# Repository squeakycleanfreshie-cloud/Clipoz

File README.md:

# Clipoz
The keychain that tracks movement

**What are Clipoz?**
Clipoz are small 3D printable keychains, that track movement. When the movement is triggered between certain times, a notification is sent to select Mates, telling them that your on the move!

**How are clipoz useful?**
Clipoz are perfect for school freinds, who walk the same route to school, but pass eachothers houses at different times. They tell your freind when you leave, without telling them where you are - which removes lots of privacy concens.

**Why did I create Clipoz?**
I created clipoz because I wanted to meet up with my freind at the bus stop without missing him, because he is really forgetful and won't text me. 

**Why do they look like that?**
Clipoz are themed in different fruits, printing in packs of three. I want to make them into a blind box sort of system. maybe one day.

**Assembly Instructions**
1. 3D Print the fruits body, screws and back/lid
2. Solder the parts to the custom PCB, making sure everything is good.
3. Insert the PCB into the back of the Fruits
4. Add an optional keychain if you want to
5. Setup the bot, edit the code to your setting - more info found in guide in docs.
6. Have fun using them.

Onshape Link: https://cad.onshape.com/documents/c4d0343753f5ce60cb524a63/w/d55154f7bbc865e658fab8c6/e/a9e77f0447d58db2c40de487?renderMode=0&uiState=6a01ac4ed3c7c0f6100e28a5

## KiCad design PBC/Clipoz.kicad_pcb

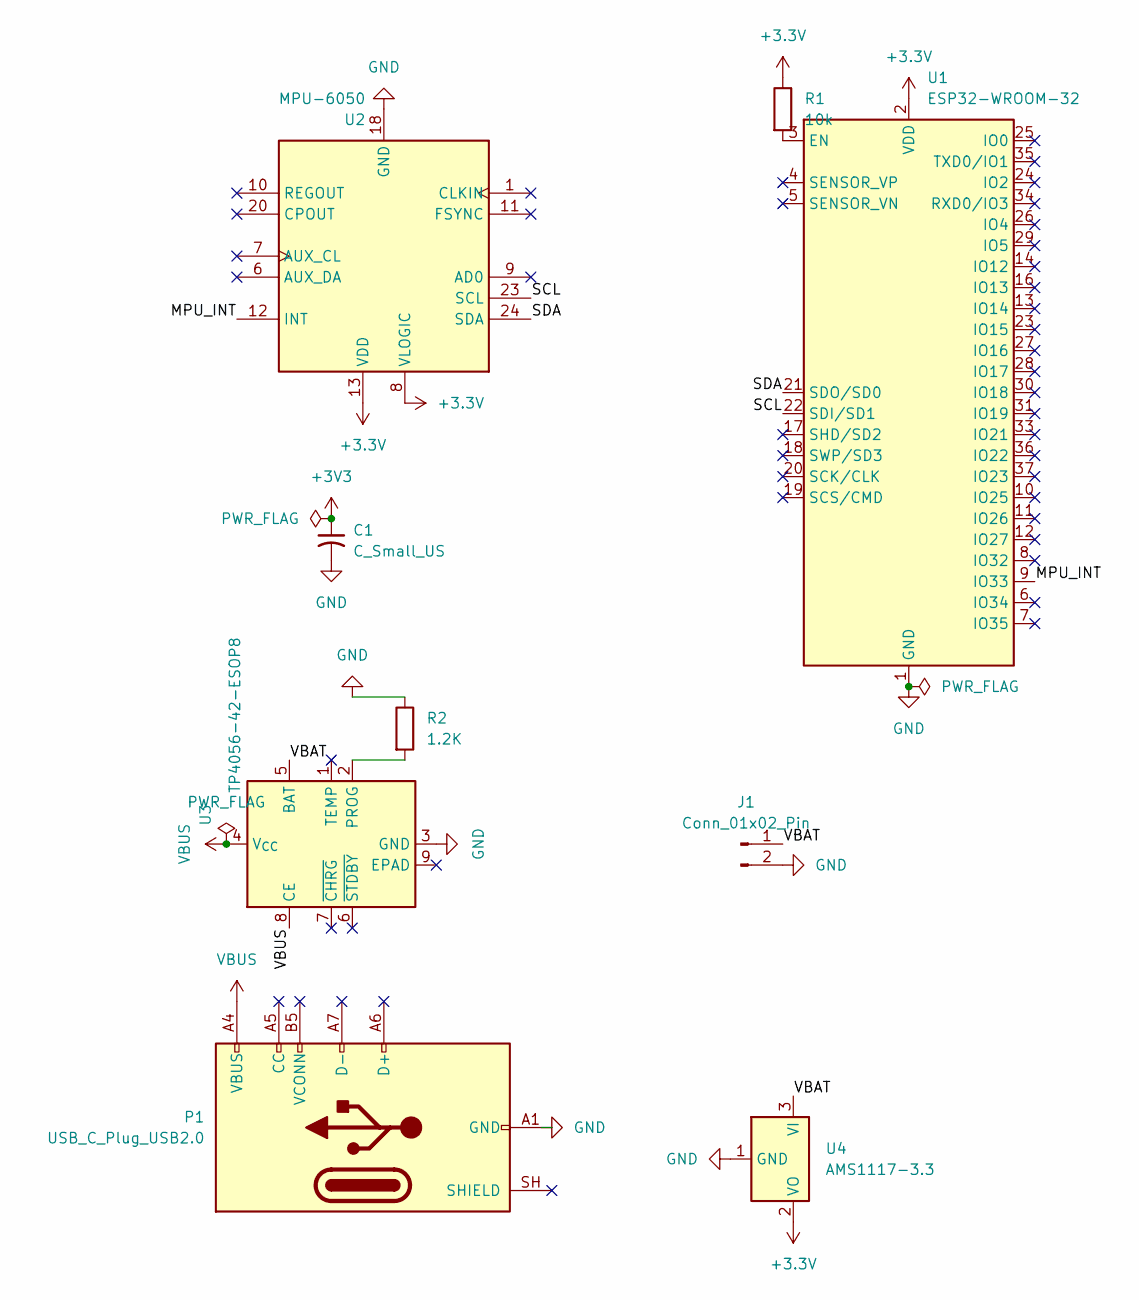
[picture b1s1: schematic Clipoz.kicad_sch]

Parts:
C1: C_Small_US; C_0402_1005Metric_Pad0.74x0.62mm_HandSolder
J1: Conn_01x02_Pin; JST_PH_S2B-PH-K_1x02_P2.00mm_Horizontal
P1: USB_C_Plug_USB2.0; USB_C_Receptacle_HRO_TYPE-C-31-M-12
R1: 10k; R_0402_1005Metric_Pad0.72x0.64mm_HandSolder
R2: 1.2K; R_0402_1005Metric_Pad0.72x0.64mm_HandSolder
U1: ESP32-WROOM-32
U2: MPU-6050; InvenSense_QFN-24_4x4mm_P0.5mm
U3: TP4056-42-ESOP8; SOIC-8-1EP_3.9x4.9mm_P1.27mm_EP2.41x3.3mm_ThermalVias
U4: AMS1117-3.3; SOT-223-3_TabPin2

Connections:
+3.3V: R1.1, U1.2 (VDD), U2.8 (VLOGIC), U2.13 (VDD), U4.2 (VO)
+3V3: C1.1
/MPU_INT: U1.9 (IO33), U2.12 (INT)
/SCL: U1.22 (SDI/SD1), U2.23 (SCL)
/SDA: U1.21 (SDO/SD0), U2.24 (SDA)
/VBAT: J1.1, U3.5 (BAT), U4.3 (VI)
GND: C1.2, J1.2, P1.A1 (GND), P1.A12 (GND), P1.B1 (GND), P1.B12 (GND), R2.1, U1.1 (GND), U1.15 (GND), U1.38 (GND), U1.39 (GND), U2.18 (GND), U3.3 (GND), U4.1 (GND)
unnamed: R1.2, U1.3 (EN)
unnamed: R2.2, U3.2 (PROG)
VBUS: P1.A4 (VBUS), P1.A9 (VBUS), P1.B4 (VBUS), P1.B9 (VBUS), U3.4 (V_{CC}), U3.8 (CE)

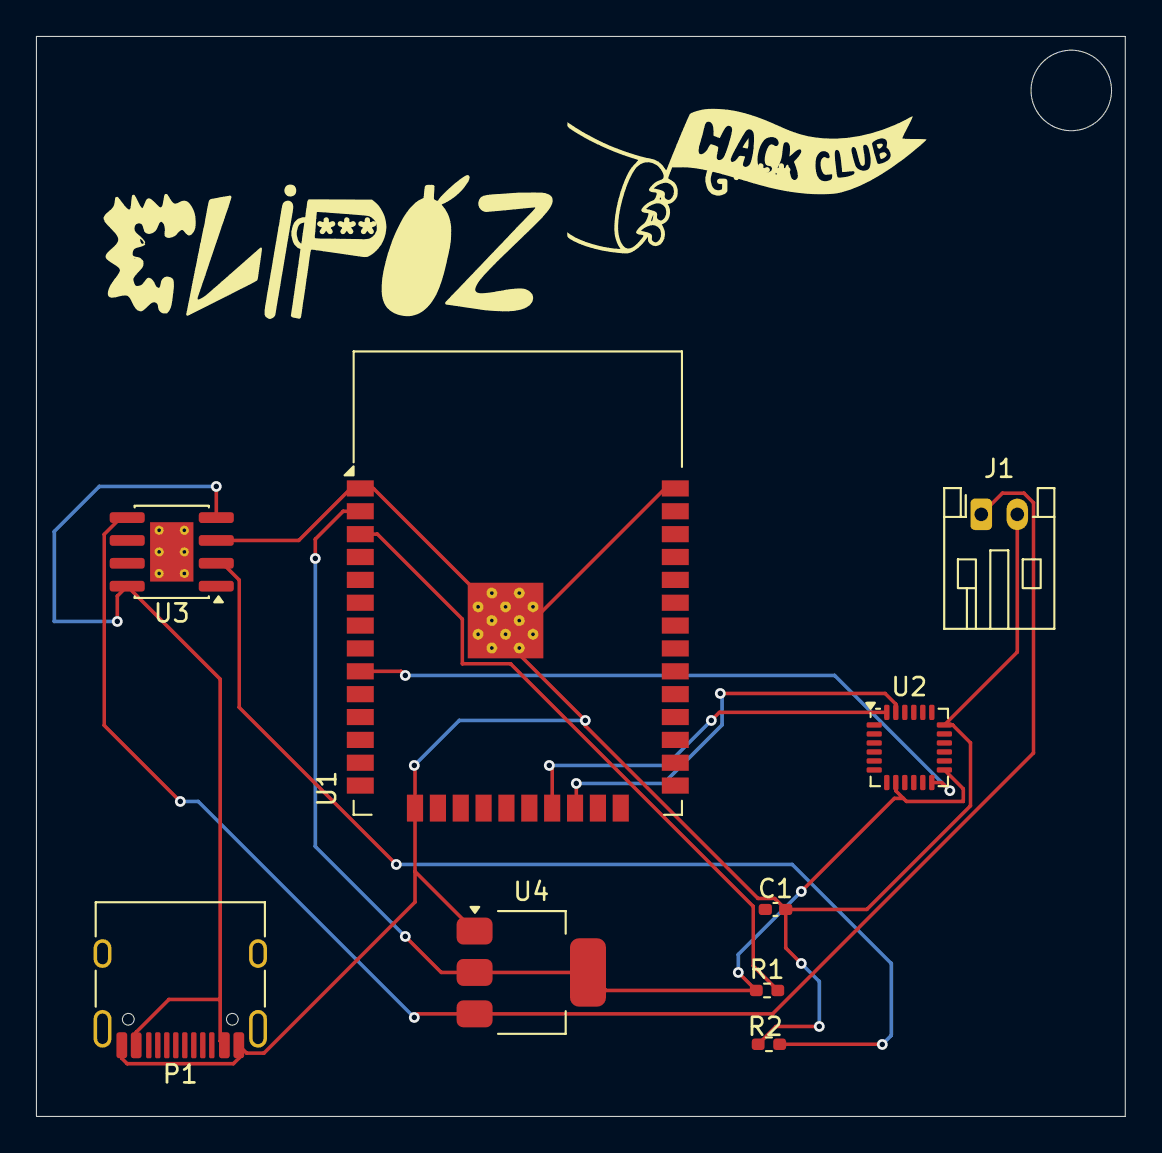
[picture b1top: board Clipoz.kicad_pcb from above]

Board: 2 copper layers, 60.5 x 60.0 mm, 9 parts (0 on the bottom side), 9 nets.

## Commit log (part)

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2026-05-10 Create PBC
2026-05-10 Create Code
2026-05-10 Create 3D MODELS
2026-05-11 Rename Bot Instructions for Github.pdf to Docs/Code Setup Instructions.pdf
2026-05-11 Rename ESP32.pdf to UnfinishedZine.pdf
2026-05-11 Rename Clipoz Cost Prices - Sheet1.csv to BOM.csv
2026-05-11 Rename ESP32 (1).pdf to Zine.pdf
